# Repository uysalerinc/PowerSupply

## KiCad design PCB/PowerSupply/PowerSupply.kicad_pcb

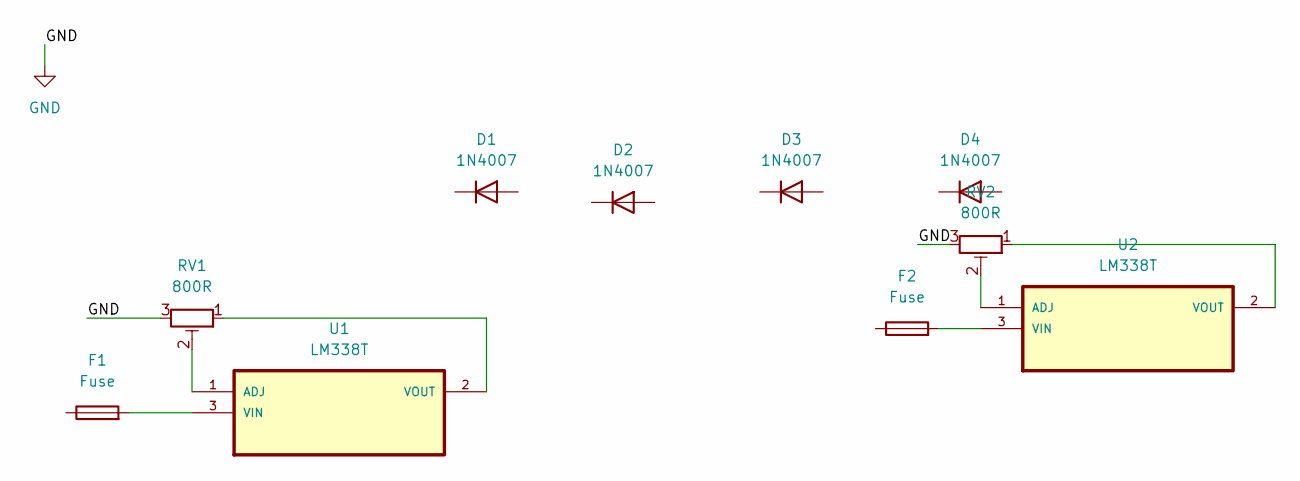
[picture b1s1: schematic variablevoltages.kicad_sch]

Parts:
D1, D2, D3, D4: 1N4007; D_DO-41_SOD81_P10.16mm_Horizontal
F1, F2: Fuse; Fuseholder_Cylinder-5x20mm_Stelvio-Kontek_PTF78_Horizontal_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
RV1, RV2: 800R; Potentiometer_Bourns_3296W_Vertical
U1, U2: LM338T; TO254P1054X470X1955-3

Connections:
GND: RV1.3, RV2.3
unnamed: RV1.2, U1.1 (ADJ)
unnamed: F1.2, U1.3 (VIN)
unnamed: RV1.1, U1.2 (VOUT)
unnamed: RV2.2, U2.1 (ADJ)
unnamed: F2.2, U2.3 (VIN)
unnamed: RV2.1, U2.2 (VOUT)

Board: 2 copper layers, 10 parts (0 on the bottom side), 7 nets, no tracks yet.

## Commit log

2024-06-29 Create LICENSE
2024-06-29 Update LICENSE
2024-06-29 remove kicad files
